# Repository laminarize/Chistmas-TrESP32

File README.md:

# Christmas TrESP32 — SmartThings Matter Christmas Tree Controller

**Manufacturer:** `Pixel Paw Studio`  
**Model:** `Christmas TrESP32`

A high-performance DIY replacement for the stock 29V DC power supply and inline foot-pedal receiver controller (e.g., **Ting Shen `TS-48W29V`** `29V DC, 1.66A, 48W` brick + **`FPTSR-053-29-20`** inline button receiver + **Polygroup `PDT-015-14`** RF remote on the Home Decorators Collection `25PG90091` 9 ft. Yorkshire Twinkling Fir and similar 2-wire bi-color trees).

Built using **ESP-IDF** and the official **`esp-matter`** SDK on an **ESP32-S3**, this controller pairs natively with **Samsung SmartThings** over local Wi-Fi via **Matter** on **1 single endpoint** and includes a **custom local SmartThings Lua Edge Driver ([`edge-driver/`](edge-driver/))** that places **Master Power**, **Ultrasonic Dimmer (`25 kHz` PWM)**, and a clean **RGB Multicolor On/Off Toggle Switch** onto **1 single SmartThings app entry** (with zero rainbow color wheels or extra room tiles).

---

## 1. Hardware Options: Custom Rev C PCB vs. Breakout Modules

You can build this controller either using our **turnkey single-board custom PCB (`hardware/`, Rev C)** or on a breadboard/enclosure using off-the-shelf breakout modules.

### Option 1: Custom Single-Board Controller PCB (`hardware/`, Rev C — Recommended)

The [`hardware/`](hardware/) directory contains a complete KiCad 9/10 hardware design and ready-to-order **JLCPCB** and **PCBWay** fabrication + turnkey PCBA files (`80 × 60 mm`, 2-layer, `1 oz` copper, minimum drill `0.30 mm`):

- **Integrated Single-Plug Power & Logic:** Steps down the `29V DC` tree power brick via a TI **`LMR51430XDDCR`** (`36V, 3A` synchronous buck $\to 5.21\text{ V}$) and low-dropout `3.3V, 1A` regulator (`U3`: `AP7361C-33E-13` / `MCP1826S-3302E/DB`) to power an onboard **`ESP32-S3-WROOM-1-N8`** (`U1`) and TI **`DRV8871DDA`** H-bridge (`U4`, `R9 = 36 kΩ` $\to 1.78\text{ A}$ current limit, solid-poured thermal pad with tented vias).
- **Full Input & Host Computer USB Protection:**
  - **Zero-Drop Reverse-Polarity & Surge Protection:** **`AOD4185`** `40V` P-MOSFET (`Q1`) + `12V` gate Zener (`D5`) + **`SMAJ30A`** TVS clamp (`D4`), paired with the `29V 2A` Class 2 power supply's built-in hiccup OCP and `DRV8871`'s `1.78A` active cycle-by-cycle current limit.
  - **Computer-Safe Dual-Supply OR-ing (`D1`, `D3`) & USB ESD (`U5`):** Automotive-qualified (`AEC-Q101`) Nexperia **`PMEG4010CEH,115`** low-leakage `40V, 1A` MEGA Schottky diodes in flat-lead `SOD-123F` isolate `USB-C VBUS` (`J3`, protected by `USBLC6-2SC6`) from `+5V_BUCK` so plugging in a laptop while `29V DC` is live can never back-feed `VBUS`.
- **Flexible Tree Wiring & Onboard Diagnostics:**
  - **`J1` (`29V_DC_IN`):** `5.08 mm` Phoenix Contact (`1729128`) screw terminal for the `29V 2A` power brick.
  - **`J2` (`TREE_29V_OUT`) + `TP1`/`TP2`:** Connect the 2-wire tree cable either via the `5.08 mm` screw terminal (`J2`) or directly to the `4 × 4 mm` (`2.0 mm` plated hole) strain-relief solder pads (`TP1`/`TP2`).
  - **Onboard Controls, LEDs & Probe Pads:** `SW1` (`RESET`), `SW2` (`BOOT` / `GPIO 0`), `D2` (`3.3V` red power LED), `D6` (`GPIO 38` green Matter status LED), and `1.5 mm` SMD diagnostic probe pads `TP3` (`+29V`), `TP4` (`+5V`), `TP5` (`+3V3`), and `TP6` (`GND`).
- **Ordering Files (`hardware/`):**
  - **Bare PCB Fabrication (JLCPCB or PCBWay):** Upload [`hardware/gerbers.zip`](hardware/gerbers.zip).
  - **JLCPCB Turnkey PCBA:** Upload [`hardware/jlcpcb_bom.csv`](hardware/jlcpcb_bom.csv) (`42` populated parts across `28` verified in-stock LCSC `Cxxxxxx` lines, with `11` Basic/Preferred lines for free feeder setup) and [`hardware/jlcpcb_positions.csv`](hardware/jlcpcb_positions.csv) (`42` CPL placements with EasyEDA pad/polarity rotation & midpoint offsets).
  - **PCBWay Turnkey PCBA:** Upload [`hardware/bom.csv`](hardware/bom.csv) (`42` populated parts across `29` unique MPN lines) and [`hardware/positions.csv`](hardware/positions.csv) (`42` native KiCad IPC-7351B placements).

| Custom Rev C PCB Signal | ESP32-S3 Pin | Connected Hardware |
| :--- | :--- | :--- |
| **`TREE_IN1` (Warm White PWM)** | `GPIO 5` (`U1` Pin 5) | `DRV8871DDA` `IN1` (`25 kHz` PWM + `100 kΩ` pull-down `R7`) |
| **`TREE_IN2` (RGB Multicolor PWM)** | `GPIO 6` (`U1` Pin 6) | `DRV8871DDA` `IN2` (`25 kHz` PWM + `100 kΩ` pull-down `R8`) |
| **`BOOT` / Factory Reset Button** | `GPIO 0` (`U1` Pin 27) | `SW2` (`3 s` hold triggers Matter factory reset) |
| **`STATUS` LED (Matter State)** | `GPIO 38` (`U1` Pin 31) | `R11` (`1 kΩ`) + `D6` (`570 nm` green `0603` LED) |
| **Native USB-C Flash / Logs** | `GPIO 19` (`D-`), `GPIO 20` (`D+`) | `J3` (`USB4105-GF-A`) via `U5` (`USBLC6-2SC6`) |

---

### Option 2: Off-the-Shelf Breakout Bill of Materials (BOM)

| Component | Recommendation | Estimated Cost | Notes |
| :--- | :--- | :--- | :--- |
| **Microcontroller** | **ESP32-S3 DevKit** (8MB or 16MB Flash) | $5 – $9 | Dual-core Xtensa LX7, 2.4 GHz Wi-Fi + BLE 5.0 for Matter commissioning. |
| **H-Bridge Driver** | **Adafruit / TI DRV8871 Breakout Board** | $3 – $8 | Rated 6.5V – 45V DC @ 3.6A peak. Includes `POWER (+/-)` and `MOTOR` screw terminals plus `GND`, `VM`, `IN1`, `IN2` logic pins. Driven at `25 kHz` ultrasonic PWM for silent dimming. |
| **Power Supply (Tree LEDs)** | **Generic 29V 2A DC Power Supply** (Amazon) | $12 – $18 | Standard 29V DC / 2A (58W) replacement power brick for 29V LED Christmas trees. |
| **ESP32 Power** | **USB-C 5V Adapter** *or* **LM2596HV Buck Converter** | $0 – $4 | Power the ESP32-S3 directly via USB-C, or step down the 29V supply to 5.0V DC using an `LM2596HV` buck converter into `5V/VIN`. |

---

## 2. Electrical Wiring Diagram

Bypass the factory inline foot-pedal / RF receiver pod (e.g., **`FPTSR-053-29-20`**) downstream of the `29V` brick and connect the `DRV8871` output directly to the 2-wire tree string. The tree uses **anti-parallel LED strings** over its 2-wire bus:
- **Polarity A (`+29V` on `OUT1`, `GND` on `OUT2` — driven by `IN1` / `GPIO 5`):** Illuminates the **Warm White** LEDs (with built-in hardware twinkling on the secondary fairy bulbs).
- **Polarity B (`GND` on `OUT1`, `+29V` on `OUT2` — driven by `IN2` / `GPIO 6`):** Illuminates the **RGB Festive Multicolor** LEDs (with built-in hardware twinkling on the secondary fairy bulbs).
- **Motor Screw Terminal Polarity:** Because 2-wire bi-color trees wire Warm White and RGB LEDs in anti-parallel across the two wires, the `MOTOR` screw terminals are **non-polarized** with respect to safety—swapping the two tree wires simply swaps which polarity corresponds to Warm White vs. RGB Multicolor. *(Always bypass any inline factory foot-pedal/RF button pod first; leaving an inline receiver pod in series blocks reverse polarity.)*

### Option A: Powering ESP32-S3 via USB-C (Recommended & Simplest)

```
                      [ 120V AC Wall Plug ]
                                │
                                ▼
                     ┌─────────────────────┐
                     │ Generic 29V 2A PSU  │
                     │ Output: 29V DC 2.0A │
                     └───────┬─────┬───────┘
                    +29V DC  │     │  -29V (GND)
                             ▼     ▼
                  ┌───────────────────────────┐
   [ 5V USB-C ]   │  DRV8871 Breakout Board   │
        │         │                           │
        ▼         │  Screw Terminals:         │
┌───────────────┐ │   POWER + <── +29V DC     │
│ ESP32-S3      │ │   POWER - <── -29V (GND)  │
│               │ │   MOTOR 1 ────────────────┼───> Tree Wire +
│  GPIO 5 (5~) ─┼─┼─> IN1                     │
│  GPIO 6 (6~) ─┼─┼─> IN2     MOTOR 2 ────────┼───> Tree Wire -
│  GND ─────────┼─┼─> GND                     │
└───────────────┘ │  (VM pin is internally    │
                  │   tied to POWER +)        │
                  └───────────────────────────┘
```

### Option B: Single-Plug Power via LM2596HV Buck Converter (29V $\to$ 5.0V)

```
                      [ 120V AC Wall Plug ]
                                │
                                ▼
                     ┌─────────────────────┐
                     │ Generic 29V 2A PSU  │
                     │ Output: 29V DC 2.0A │
                     └──────────┬──────────┘
                                │  +29V DC & GND
                 ┌──────────────┴──────────────┐
                 │                             │
                 ▼                             ▼
      ┌────────────────────┐        ┌──────────────────────────┐
      │ LM2596HV Buck      │        │ DRV8871 Breakout Board   │
      │ IN+:  +29V DC      │        │ POWER + (VM): +29V DC    │
      │ IN-:  GND (Common) │        │ POWER - / GND: Common GND│
      │ OUT+: +5.0V DC     │        │ IN1: <── ESP32 GPIO 5    │
      │ OUT-: GND (Common) │        │ IN2: <── ESP32 GPIO 6    │
      └──────────┬─────────┘        │ MOTOR 1 ──┐              │
                 │ +5.0V            │ MOTOR 2 ──┼─┐            │
                 ▼                  └───────────┼─┼────────────┘
      ┌────────────────────┐                    │ │
      │ ESP32-S3 DevKit    │                    │ │
      │ 5V / VIN <── (+5V) │                    │ │
      │ GND      <── (GND) │                    │ │
      │ GPIO 5 (5~) ──> IN1│                    │ │
      │ GPIO 6 (6~) ──> IN2│                    │ │
      └────────────────────┘                    ▼ ▼
                                     ┌──────────────────────┐
                                     │ Tree 2-Pin Connector │
                                     │ Wire + : MOTOR 1     │
                                     │ Wire - : MOTOR 2     │
                                     └──────────────────────┘
```

### Pin Summary Table

| DRV8871 Pin / Terminal | Connected To | Purpose |
| :--- | :--- | :--- |
| **`POWER +`** (Screw Terminal) | `29V 2A PSU` **`+29V`** | High-voltage motor/LED supply (`29V DC`) |
| **`POWER -`** (Screw Terminal) | `29V 2A PSU` **`-` (`GND`)** | High-voltage return ground (internally tied to `GND` pin) |
| **`GND`** (Through-Hole Pin) | **ESP32-S3 `GND`** | Common logic ground reference between ESP32 and DRV8871 |
| **`VM`** (Through-Hole Pin) | *Leave unconnected* | Internally connected to `POWER +` on the breakout board |
| **`IN1`** (Through-Hole Pin) | **ESP32-S3 `GPIO 5` (`5~`)** | `25 kHz` PWM input for **Warm White** (`Polarity A`) |
| **`IN2`** (Through-Hole Pin) | **ESP32-S3 `GPIO 6` (`6~`)** | `25 kHz` PWM input for **RGB Multicolor** (`Polarity B`) |
| **`MOTOR`** (Screw Terminals) | **Tree `+` and `-` Cable** | Switched `29V` H-bridge output to the tree LED strings |

> [!CAUTION]
> **If using an LM2596HV Buck Converter:** Connect the 29V power supply to the buck converter inputs (`IN+` and `IN-`) **before** connecting the ESP32. Measure `OUT+` and `OUT-` with a multimeter and adjust the trim pot to **5.0V DC** before wiring `OUT+` to the ESP32 `5V/VIN` pin.

---

## 3. Single-Entry SmartThings UI & Local Edge Driver (`edge-driver/`)

`Christmas TrESP32` exposes **only 1 Matter Endpoint (`Endpoint 1`)** on the ESP32-S3 and ships with a local Lua Edge Driver ([`edge-driver/`](edge-driver/)) that runs directly on your SmartThings Hub over LAN, presenting **1 single device entry** in the SmartThings app with two clean sections on the same card:

| Card Section (Single App Entry) | SmartThings UI Control | Endpoint 1 Matter Mapping | Behavior |
| :--- | :--- | :--- | :--- |
| **`main` (`Christmas TrESP32`)** | **Master Power Button + Dimmer Slider (`1% – 100%`)** | `OnOff` (`OnOff`) & `LevelControl` (`CurrentLevel`) | • **Power Button:** Turns the tree completely On or Off.<br>• **Dimmer Slider:** Smoothly dims the active polarity (`1 – 254`, reaching true `100%` unchopped DC at max) via silent `25 kHz` PWM, which also naturally scales the hardware fairy-bulb twinkle pace. |
| **`rgbMode` (`RGB Multicolor`)** | **Simple On / Off Toggle Switch** *(same screen, below Dimmer)* | `ColorControl` (`ColorTemperatureMireds`: `455` = OFF, `154` = ON) | • **Toggle OFF:** **Warm White** (`Polarity A` / `GPIO 5` / `IN1`).<br>• **Toggle ON:** **RGB Festive Multicolor** (`Polarity B` / `GPIO 6` / `IN2`). |
| **Routines & Settings (`⋮ -> Settings`)** | **Preferred Turn-On / Turn-Off Dim Levels (`0% – 100%`)** | `LevelControl` (`MoveToLevelWithOnOff` & `MoveToLevel` while OFF) | • **SmartThings Routines:** Supports both **Turn On + Dimmer %** and **Turn Off + pre-staged Dimmer %** (stages brightness without turning the tree back on).<br>• **Card Power-On / Power-Off Schedules:** Set **Preferred Turn-On Dim Level (%)** and/or **Preferred Dim Level on Turn-Off (%)** in `More (⋮) -> Settings`. |

### Installing the Local SmartThings Edge Driver to Your Hub (One-Time Setup)

Run the included helper script on macOS:
```bash
./deploy-edge-driver.sh
```
This installs Samsung's official `@smartthings/cli` via Homebrew (if not already installed), opens a one-time browser login to your Samsung account, creates/enrolls a local Edge channel on your SmartThings Hub if needed, and packages + installs [`edge-driver/`](edge-driver/) straight onto your Hub (`smartthings edge:drivers:package edge-driver -I`).

- **If `Christmas TrESP32` is already paired in SmartThings:** Open its card $\to$ **More (`⋮`) $\to$ Driver $\to$ Select a different driver** $\to$ choose **`Christmas TrESP32`**.
- **If pairing fresh:** Scan the Matter QR/manual code as usual—the Hub automatically matches `VendorId = 0xFFF1` / `ProductId = 0x8000` to **`Christmas TrESP32`**.

---

## 4. Contained Build & Flash Workflow

This project uses a self-contained build and flash workflow on macOS:
- **Build Environment (Docker):** Compiles inside the official `espressif/esp-matter` container (`ESP-IDF v6.0.2`).
- **Flashing & Serial Monitor (Local `.venv`):** Uses a lightweight Python virtual environment (`.venv`) with `esptool` and `pyserial` on the macOS host to communicate with `/dev/cu.usbmodem*`.

### Step 1: Build the Firmware in Docker
Ensure Docker Desktop is running, then run:
```bash
./build-docker.sh
```
This compiles `build/christmas_tree_matter.bin`, `build/bootloader/bootloader.bin`, and `build/partition_table/partition-table.bin`.

### Step 2: Flash to ESP32-S3
Plug the ESP32-S3 into your Mac via USB and run:
```bash
./flash.sh
```

Additional `./flash.sh` commands:
```bash
./flash.sh info       # Read ESP32-S3 chip info and MAC address
./flash.sh monitor    # Open 115200-baud serial monitor (Ctrl+] to exit)
./flash.sh erase      # Erase entire flash (clears NVS & Matter fabrics)
```

---

## 5. Pairing & Resetting with Samsung SmartThings

### Commissioning Steps
1. Open the serial monitor (`./flash.sh monitor`) and press the `RST` button on the ESP32-S3. On boot, the firmware prints a `SetupQRCode` URL and an 11-digit `Manual pairing code` to the serial console.
2. Open the **Samsung SmartThings** app on your phone (connected to your **2.4 GHz Wi-Fi** network with Bluetooth enabled).
3. Tap **"+"** $\to$ **Add device** $\to$ **Scan QR code** (or **Partner devices** $\to$ **Matter**).
4. Scan the generated QR code or enter the 11-digit manual pairing code displayed in your serial console.
5. If prompted about an **Uncertified Accessory**, tap **Add Anyway**.

### Resetting, Pairing & `STATUS` LED (`GPIO 38`) States
- **Onboard `STATUS` LED (`GPIO 38` / Rev C `D6`):**
  - **`1 Hz` Blink (`500 ms` ON / `500 ms` OFF):** Uncommissioned or Matter commissioning window open (ready to pair over BLE).
  - **`2.5 Hz` Blink (`200 ms` ON / `200 ms` OFF):** Matter `Identify` command active from SmartThings / Matter controller.
  - **`5 Hz` Rapid Blink (`100 ms` ON / `100 ms` OFF):** `BOOT` button (`GPIO 0`) is currently held down during the 3-second factory-reset countdown.
  - **Solid ON:** Commissioned onto a Matter fabric and operating normally.
- **Automatic Reset on Delete:** Whenever you delete the device from the SmartThings app while it is online, the firmware intercepts `DeviceEventType::kFabricRemoved` and automatically runs `esp_matter::factory_reset()`, wiping all fabrics and immediately restarting BLE pairing advertisements.
- **Physical `BOOT` Button Reset (3-Second Hold):** Hold down the **`BOOT`** button (`GPIO 0` / `SW2`) on the ESP32-S3 for **3 seconds** at any time to trigger a Matter factory reset and reopen BLE pairing mode without needing a computer.
- **USB Erase:** Run `./flash.sh erase && ./flash.sh flash` over USB.

> [!TIP]
> **iPhone / iOS Re-Pairing Tip (Error `39-900`):**
> When pairing via an iPhone, iOS first commissions the device into the Apple Home / iOS Matter Keychain before handing it off to the SmartThings Hub. If you delete the device and re-pair later, check **iPhone Settings $\to$ General $\to$ Matter Accessories** and remove any leftover entry for the device first so iOS does not attempt to reuse a deleted fabric. Also ensure your iPhone, SmartThings Hub, and ESP32 are on the same 2.4 GHz Wi-Fi subnet with local network access enabled for SmartThings.

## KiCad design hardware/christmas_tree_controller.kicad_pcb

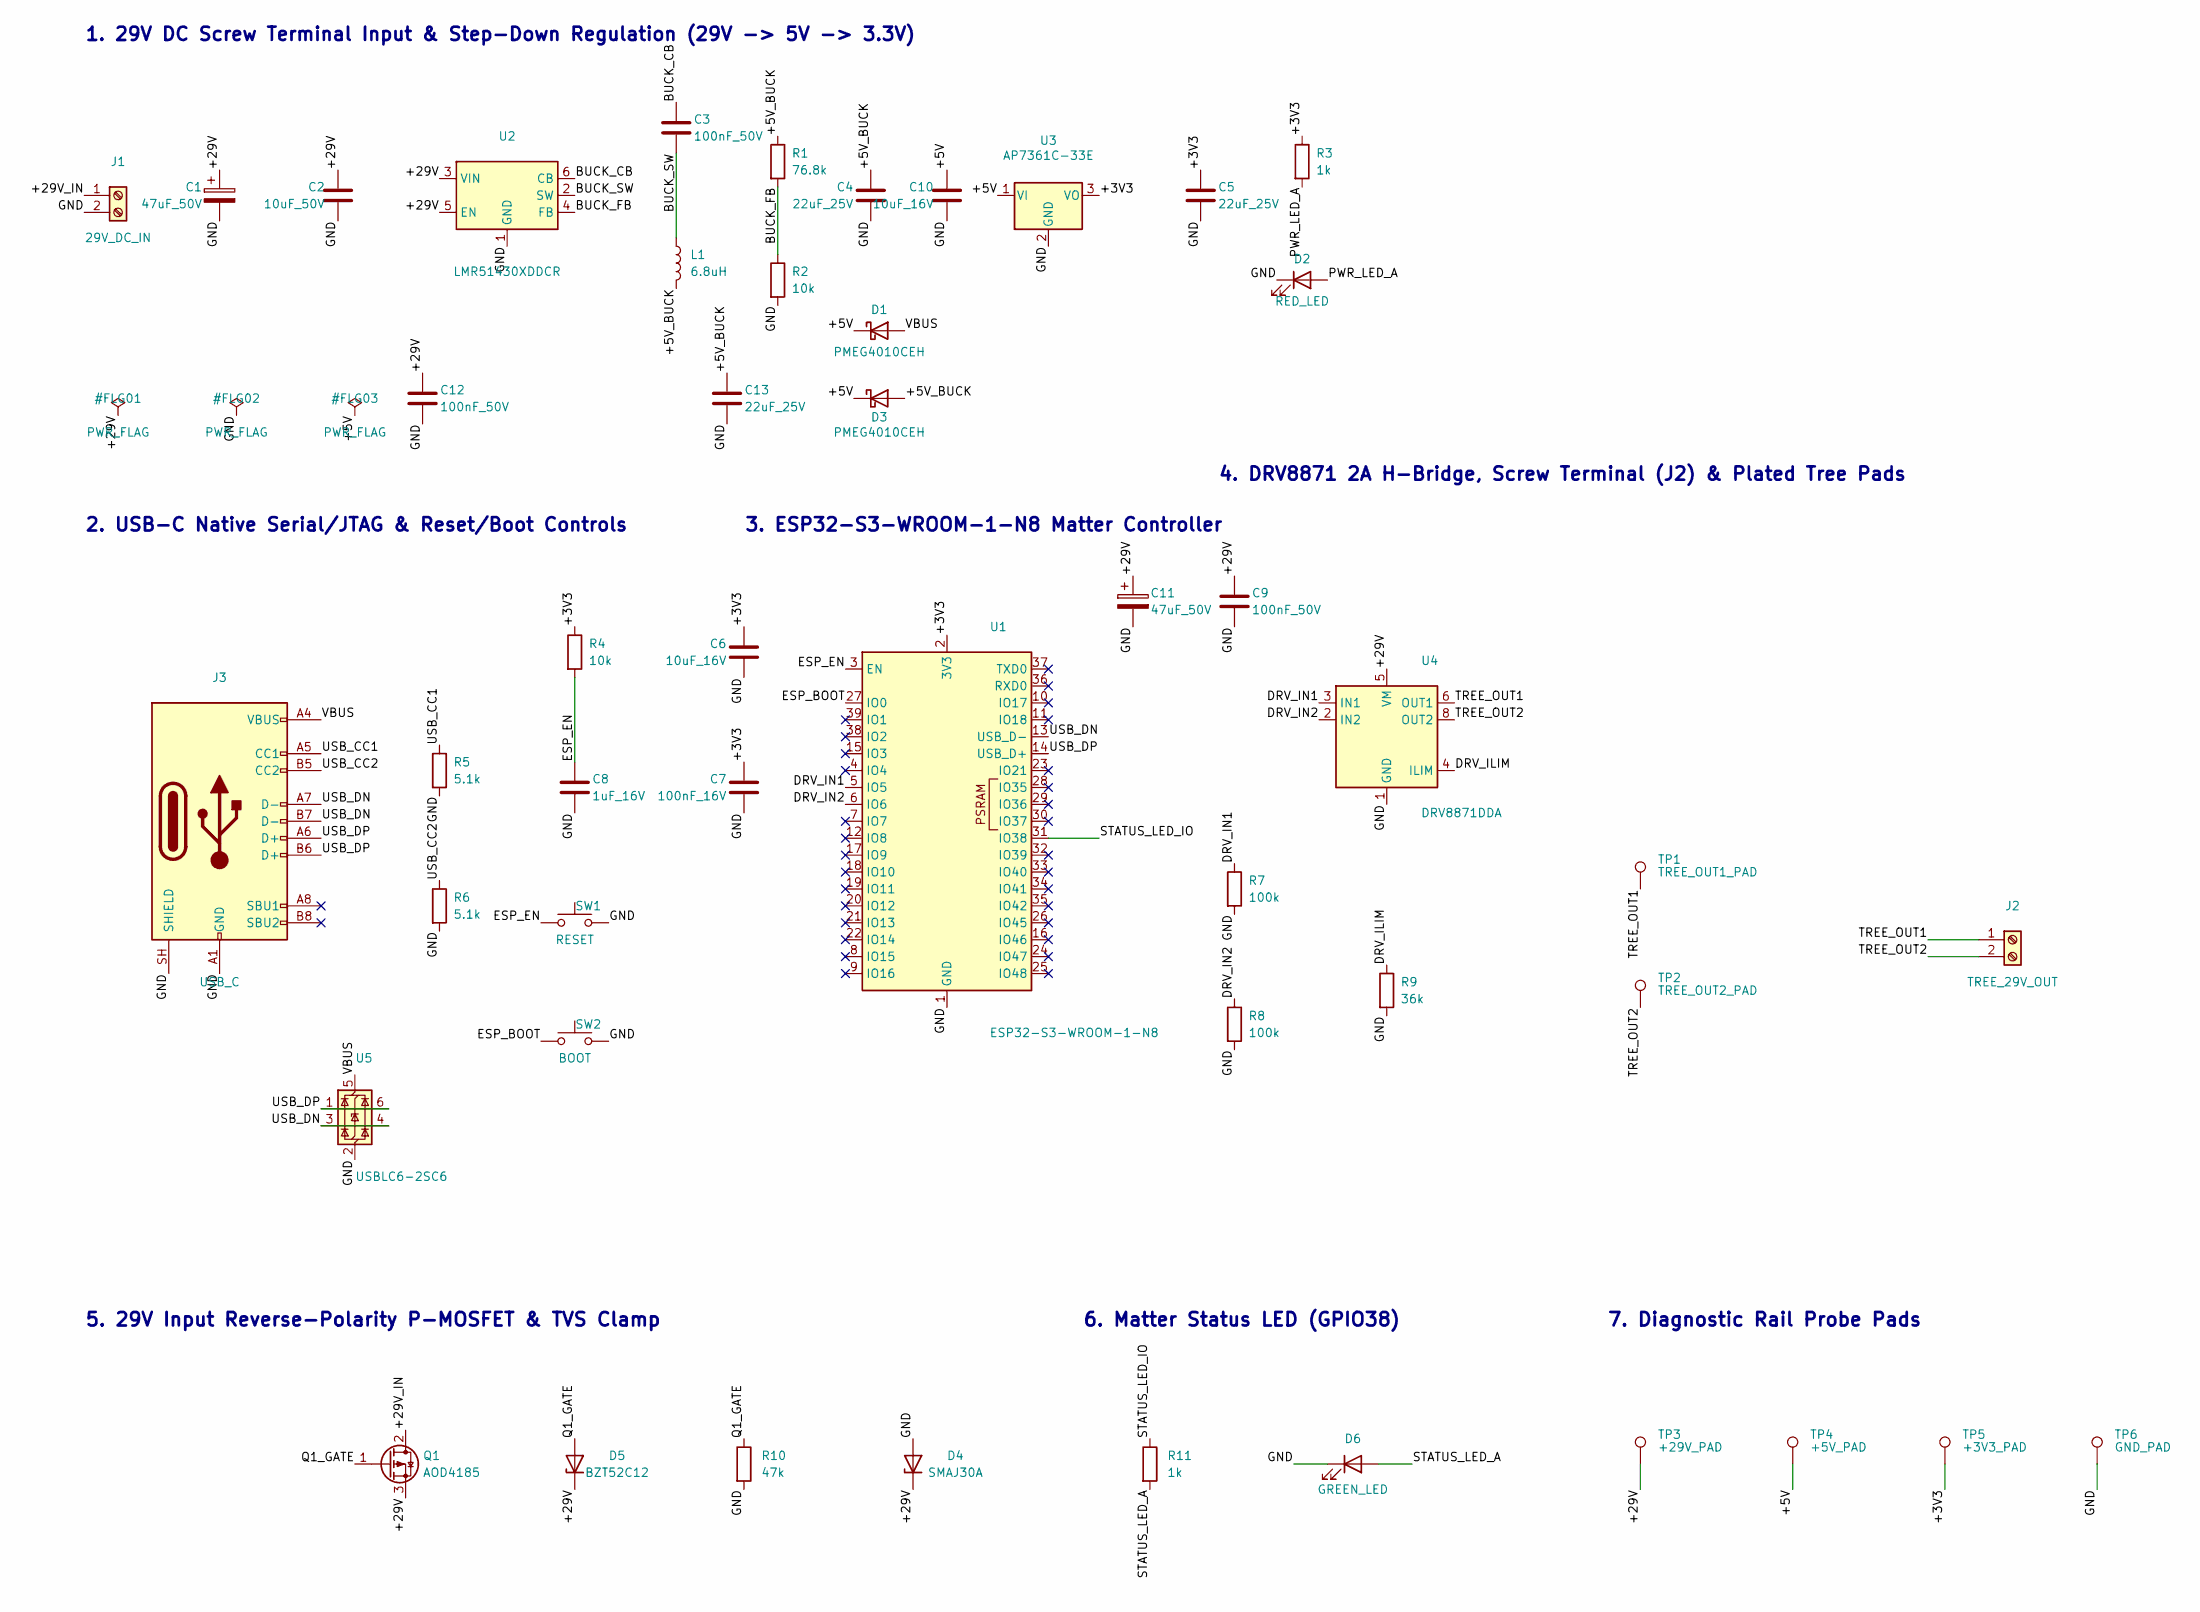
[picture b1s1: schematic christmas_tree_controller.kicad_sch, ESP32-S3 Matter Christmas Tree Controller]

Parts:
C1, C11: 47uF_50V; CP_Elec_6.3x7.7; MPN EEE-FK1H470P
C2: 10uF_50V; C_1210_3225Metric; MPN GRM32ER71H106KA12L
C3, C9, C12: 100nF_50V; C_0603_1608Metric; MPN CC0603KRX7R9BB104
C4, C5, C13: 22uF_25V; C_0805_2012Metric; MPN CL21A226MAQNNNE
C6, C10: 10uF_16V; C_0805_2012Metric; MPN CL21B106KOQNNNE
C7: 100nF_16V; C_0603_1608Metric; MPN CC0603KRX7R7BB104
C8: 1uF_16V; C_0603_1608Metric; MPN CL10B105KO8NNNC
D1, D3: PMEG4010CEH; D_SOD-123F; MPN PMEG4010CEH,115
D2: RED_LED; LED_0603_1608Metric; MPN 150060RS75000
D4: SMAJ30A; D_SMA; MPN SMAJ30A
D5: BZT52C12; D_SOD-123; MPN BZT52C12-7-F
D6: GREEN_LED; LED_0603_1608Metric; MPN 150060VS75000
J1: 29V_DC_IN; TerminalBlock_Phoenix_MKDS-1,5-2-5.08_1x02_P5.08mm_Horizont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; MPN 1729128
J2: TREE_29V_OUT; TerminalBlock_Phoenix_MKDS-1,5-2-5.08_1x02_P5.08mm_Horizont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; MPN 1729128
J3: USB_C; USB_C_Receptacle_GCT_USB4105-xx-A_16P_TopMnt_Horizontal; MPN USB4105-GF-A
L1: 6.8uH; L_Bourns_SRN6045TA; MPN SRN6045TA-6R8M
Q1: AOD4185; TO-252-2; MPN AOD4185
R1: 76.8k; R_0603_1608Metric; MPN RC0603FR-0776K8L
R2, R4: 10k; R_0603_1608Metric; MPN RC0603FR-0710KL
R3, R11: 1k; R_0603_1608Metric; MPN RC0603FR-071KL
R5, R6: 5.1k; R_0603_1608Metric; MPN RC0603FR-075K1L
R7, R8: 100k; R_0603_1608Metric; MPN RC0603FR-07100KL
R9: 36k; R_0603_1608Metric; MPN RC0603FR-0736KL
R10: 47k; R_0603_1608Metric; MPN RC0603FR-0747KL
SW1: RESET; SW_SPST_B3U-1000P-B; MPN B3U-1000P-B
SW2: BOOT; SW_SPST_B3U-1000P-B; MPN B3U-1000P-B
TP1: TREE_OUT1_PAD; TestPoint_THTPad_4.0x4.0mm_Drill2.0mm
TP2: TREE_OUT2_PAD; TestPoint_THTPad_4.0x4.0mm_Drill2.0mm
TP3: +29V_PAD; TestPoint_Pad_D1.5mm
TP4: +5V_PAD; TestPoint_Pad_D1.5mm
TP5: +3V3_PAD; TestPoint_Pad_D1.5mm
TP6: GND_PAD; TestPoint_Pad_D1.5mm
U1: ESP32-S3-WROOM-1-N8; ESP32-S3-WROOM-1_0.3mmVias; MPN ESP32-S3-WROOM-1-N8
U2: LMR51430XDDCR; SOT-23-6; MPN LMR51430XDDCR
U3: AP7361C-33E; SOT-223-3_TabPin2; MPN AP7361C-33E-13
U4: DRV8871DDA; DRV8871DDA_HTSOP-8-1EP_TentedWindowed; MPN DRV8871DDAR
U5: USBLC6-2SC6; SOT-23-6; MPN USBLC6-2SC6

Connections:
/+3V3: C5.1, C6.1, C7.1, R3.1, R4.1, TP5.1, U1.2 (3V3), U3.3 (VO)
/+5V: C10.1, D1.1 (K), D3.1 (K), TP4.1, U3.1 (VI)
/+5V_BUCK: C4.1, C13.1, D3.2 (A), L1.2, R1.1
/+29V: C1.1, C2.1, C9.1, C11.1, C12.1, D4.1 (K), D5.1 (K), Q1.3 (S), TP3.1, U2.3 (VIN), U2.5 (EN), U4.5 (VM)
/+29V_IN: J1.1, Q1.2 (D)
/BUCK_CB: C3.1, U2.6 (CB)
/BUCK_FB: R1.2, R2.1, U2.4 (FB)
/BUCK_SW: C3.2, L1.1, U2.2 (SW)
/DRV_ILIM: R9.1, U4.4 (ILIM)
/DRV_IN1: R7.1, U1.5 (IO5), U4.3 (IN1)
/DRV_IN2: R8.1, U1.6 (IO6), U4.2 (IN2)
/ESP_BOOT: SW2.1, U1.27 (IO0)
/ESP_EN: C8.1, R4.2, SW1.1, U1.3 (EN)
/GND: C1.2, C2.2, C4.2, C5.2, C6.2, C7.2, C8.2, C9.2, C10.2, C11.2, C12.2, C13.2, D2.1 (K), D4.2 (A), D6.1 (K), J1.2, J3.A1 (GND), J3.A12 (GND), J3.B1 (GND), J3.B12 (GND), J3.SH (SHIELD), R2.2, R5.2, R6.2, R7.2, R8.2, R9.2, R10.2, SW1.2, SW2.2, TP6.1, U1.1 (GND), U1.40 (GND), U1.41 (GND), U2.1 (GND), U3.2 (GND), U4.1 (GND), U4.7 (GND), U4.9 (GND), U5.2 (GND)
/PWR_LED_A: D2.2 (A), R3.2
/Q1_GATE: D5.2 (A), Q1.1 (G), R10.1
/STATUS_LED_A: D6.2 (A), R11.2
/STATUS_LED_IO: R11.1, U1.31 (IO38)
/TREE_OUT1: J2.1, TP1.1, U4.6 (OUT1)
/TREE_OUT2: J2.2, TP2.1, U4.8 (OUT2)
/USB_CC1: J3.A5 (CC1), R5.1
/USB_CC2: J3.B5 (CC2), R6.1
/USB_DN: J3.A7 (D-), J3.B7 (D-), U1.13 (USB_D-), U5.3 (I/O2), U5.4 (I/O2)
/USB_DP: J3.A6 (D+), J3.B6 (D+), U1.14 (USB_D+), U5.1 (I/O1), U5.6 (I/O1)
/VBUS: D1.2 (A), J3.A4 (VBUS), J3.A9 (VBUS), J3.B4 (VBUS), J3.B9 (VBUS), U5.5 (VBUS)

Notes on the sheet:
1. 29V DC Screw Terminal Input & Step-Down Regulation (29V -> 5V -> 3.3V)
2. USB-C Native Serial/JTAG & Reset/Boot Controls
3. ESP32-S3-WROOM-1-N8 Matter Controller
4. DRV8871 2A H-Bridge, Screw Terminal (J2) & Plated Tree Pads
5. 29V Input Reverse-Polarity P-MOSFET & TVS Clamp
6. Matter Status LED (GPIO38)
7. Diagnostic Rail Probe Pads

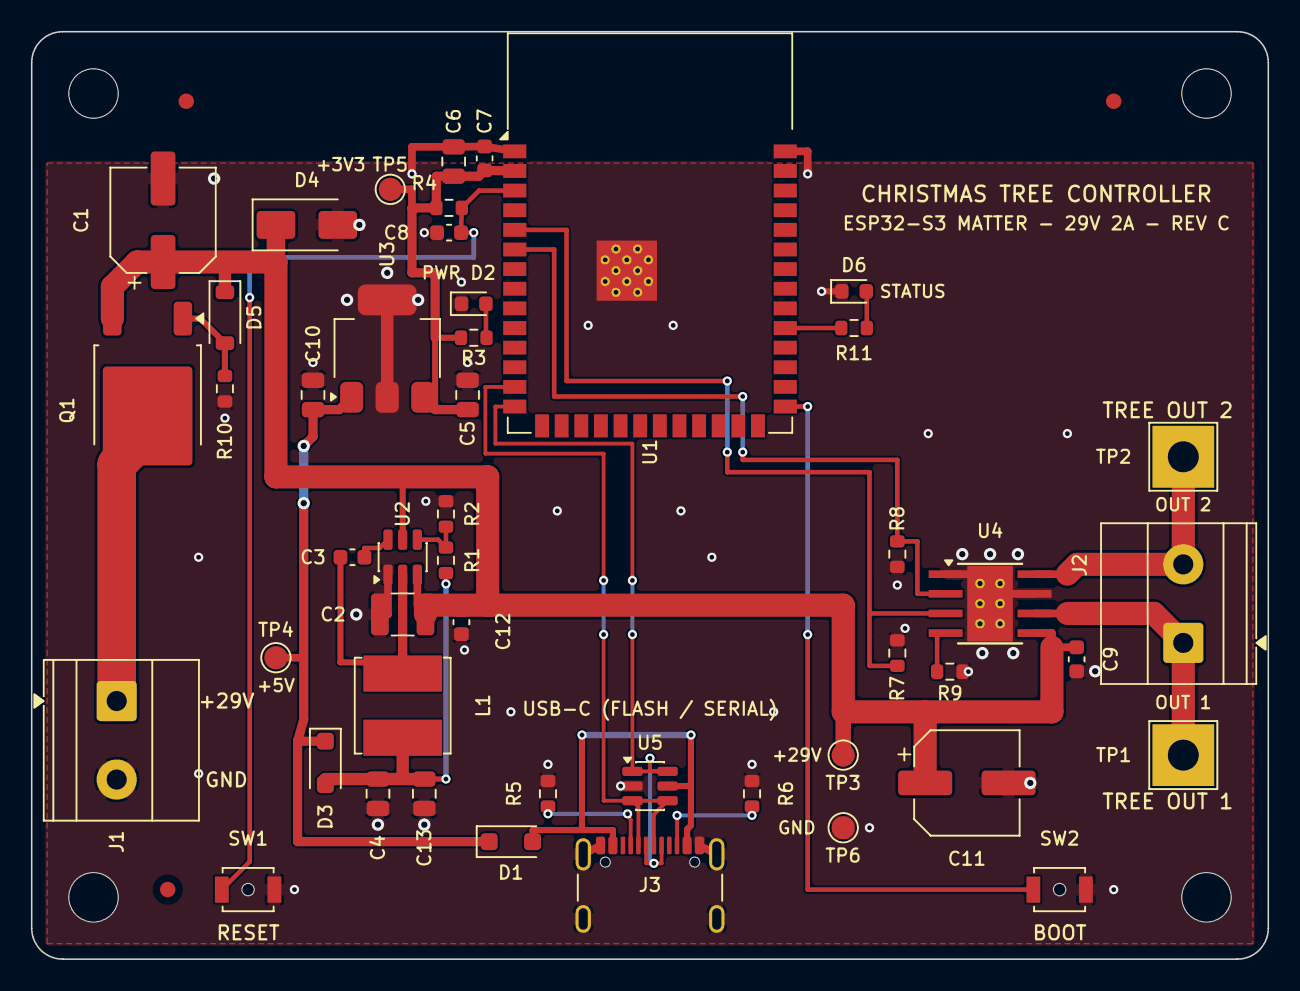
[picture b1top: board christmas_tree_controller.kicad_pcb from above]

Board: 2 copper layers, 80.0 x 60.0 mm, 55 parts (0 on the bottom side), 25 nets.

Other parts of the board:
FID1, FID2, FID3: Fiducial_1mm_Mask2mm
MH1, MH2, MH3, MH4: MountingHole_3.2mm_M3

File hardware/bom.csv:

Reference,Qty,Value,Footprint,Manufacturer,MPN,Description
"C1, C11",2,47uF_50V,Capacitor_SMD:CP_Elec_6.3x7.7,Panasonic,EEE-FK1H470P,Polarized capacitor
C2,1,10uF_50V,Capacitor_SMD:C_1210_3225Metric,Murata,GRM32ER71H106KA12L,Unpolarized capacitor
"C3, C9, C12",3,100nF_50V,Capacitor_SMD:C_0603_1608Metric,Yageo,CC0603KRX7R9BB104,Unpolarized capacitor
"C4, C5, C13",3,22uF_25V,Capacitor_SMD:C_0805_2012Metric,Samsung Electro-Mechanics,CL21A226MAQNNNE,Unpolarized capacitor
"C6, C10",2,10uF_16V,Capacitor_SMD:C_0805_2012Metric,Samsung Electro-Mechanics,CL21B106KOQNNNE,Unpolarized capacitor
C7,1,100nF_16V,Capacitor_SMD:C_0603_1608Metric,Yageo,CC0603KRX7R7BB104,Unpolarized capacitor
C8,1,1uF_16V,Capacitor_SMD:C_0603_1608Metric,Samsung Electro-Mechanics,CL10B105KO8NNNC,Unpolarized capacitor
"D1, D3",2,PMEG4010CEH,Diode_SMD:D_SOD-123F,Nexperia,"PMEG4010CEH,115","40V 1A Low-Leakage MEGA Schottky Barrier Rectifier, AEC-Q101, SOD-123F"
D2,1,RED_LED,LED_SMD:LED_0603_1608Metric,Wurth Elektronik,150060RS75000,Light emitting diode
D4,1,SMAJ30A,Diode_SMD:D_SMA,Littelfuse,SMAJ30A,Zener diode
D5,1,BZT52C12,Diode_SMD:D_SOD-123,Diodes Incorporated,BZT52C12-7-F,Zener diode
D6,1,GREEN_LED,LED_SMD:LED_0603_1608Metric,Wurth Elektronik,150060VS75000,"Light emitting diode, Green 570nm, 0603"
"J1, J2",2,29V_DC_IN / TREE_29V_OUT,"TerminalBlock_Phoenix:TerminalBlock_Phoenix_MKDS-1,5-2-5.08_1x02_P5.08mm_Horizontal",Phoenix Contact,1729128,"Generic screw terminal, single row, 01x02, script generated (kicad-library-utils/schlib/autogen/connector/)"
J3,1,USB_C,Connector_USB:USB_C_Receptacle_GCT_USB4105-xx-A_16P_TopMnt_Horizontal,GCT,USB4105-GF-A,USB 2.0-only 16P Type-C Receptacle connector
L1,1,6.8uH,Inductor_SMD:L_Bourns_SRN6045TA,Bourns,SRN6045TA-6R8M,Inductor
Q1,1,AOD4185,Package_TO_SOT_SMD:TO-252-2,Alpha & Omega Semiconductor,AOD4185,"P-MOSFET transistor, gate/drain/source"
R1,1,76.8k,Resistor_SMD:R_0603_1608Metric,Yageo,RC0603FR-0776K8L,Resistor
"R2, R4",2,10k,Resistor_SMD:R_0603_1608Metric,Yageo,RC0603FR-0710KL,Resistor
"R3, R11",2,1k,Resistor_SMD:R_0603_1608Metric,Yageo,RC0603FR-071KL,Resistor
"R5, R6",2,5.1k,Resistor_SMD:R_0603_1608Metric,Yageo,RC0603FR-075K1L,Resistor
"R7, R8",2,100k,Resistor_SMD:R_0603_1608Metric,Yageo,RC0603FR-07100KL,Resistor
R9,1,36k,Resistor_SMD:R_0603_1608Metric,Yageo,RC0603FR-0736KL,Resistor
R10,1,47k,Resistor_SMD:R_0603_1608Metric,Yageo,RC0603FR-0747KL,Resistor
"SW1, SW2",2,RESET / BOOT,Button_Switch_SMD:SW_SPST_B3U-1000P-B,Omron,B3U-1000P-B,"Push button switch, generic, two pins"
U1,1,ESP32-S3-WROOM-1-N8,Project_Footprints:ESP32-S3-WROOM-1_0.3mmVias,Espressif Systems,ESP32-S3-WROOM-1-N8,"RF Module, ESP32-S3 SoC, Wi-Fi 802.11b/g/n, Bluetooth, BLE, 32-bit, 3.3V, onboard antenna, SMD"
U2,1,LMR51430XDDCR,Package_TO_SOT_SMD:SOT-23-6,Texas Instruments,LMR51430XDDCR,"4.5-V to 36-V, 3-A synchronous buck converter with 40-µA IQ, SOT-23-6"
U3,1,AP7361C-33E,Package_TO_SOT_SMD:SOT-223-3_TabPin2,Diodes Incorporated,AP7361C-33E-13,"1A Low Dropout regulator, positive, 3.3V fixed output, SOT-223"
U4,1,DRV8871DDA,Project_Footprints:DRV8871DDA_HTSOP-8-1EP_TentedWindowed,Texas Instruments,DRV8871DDAR,"Brushed DC Motor Driver, PWM Control, 45V, 3.6A, Current limiting, HTSOP-8"
U5,1,USBLC6-2SC6,Package_TO_SOT_SMD:SOT-23-6,STMicroelectronics,USBLC6-2SC6,"Very low capacitance ESD protection diode, 2 data-line, SOT-23-6"
